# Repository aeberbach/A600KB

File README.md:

# A600KB: Mechanical keyboard Amiga A600

Like my A1200 project (see my other repos) this is a mechanical keyboard for an Amiga computer.

To make one you need:
- PCBs, which you can make by sending the contents of the 'fab' folder to your local PCB maker.
- 3D printed parts: the STL files are in the STL folder. I used a Prusa MK3S 0.25mm nozzle, Urban Grey PETG.
- 78 MX PCB-mount switches
- 32-way FFC connector (Mouser part number 538-52044-3245)
- 32-way ribbon cable (Mouser part number 538-15168-0400)
- keyswitch stabiliser for Tab and Enter keys
- one 3mm LED for CapsLock
- keycaps

For more details about design choices and putting it together please see the article on grayunicorn.com. 

Enjoy!

May 2022 Update - this is now release 2. Apart from correcting swapped keys that existed in revision 1 (see below) I made a lot of traces simpler. I used KiCAD 6 for this, it just keeps getting better. If you build a revision 2 I would love to hear about it.

Revision 1 Errata:
Many people have built it and never noticed. That goes for me too - one person contacted me and said they were having trouble with some music tracker software because it relies on the keys that are not in the right place. I had not noticed because I had not been using software that relied on those
keys - sorry if you were affected! The revision 1 PCB should be modified:

- Line 5: disconnect from MX63 (< ,) column; connect to MX79 (" ') column
- Line 7: disconnect from MX79 (" ') column; connect to MX63 (< ,) column
- Line 23: disconnect from MX79 (" ') row; connect to MX63 (< ,) row
- Line 26: disconnect from MX63 (< ,) row; connect to MX79 (" ') row

The PCB has been revised to revision 2 (the same as Commodore's schematic) now so this is fixed, but if you have a revision 1 and notice the ' and , appear to be swapped then you may need to apply this change.

Note this this project is licensed under CC BY-NC-SA 4.0 - only noncommercial use is permitted! (By all means sell the excess PCBs you get, at cost, if you order some for your own use)

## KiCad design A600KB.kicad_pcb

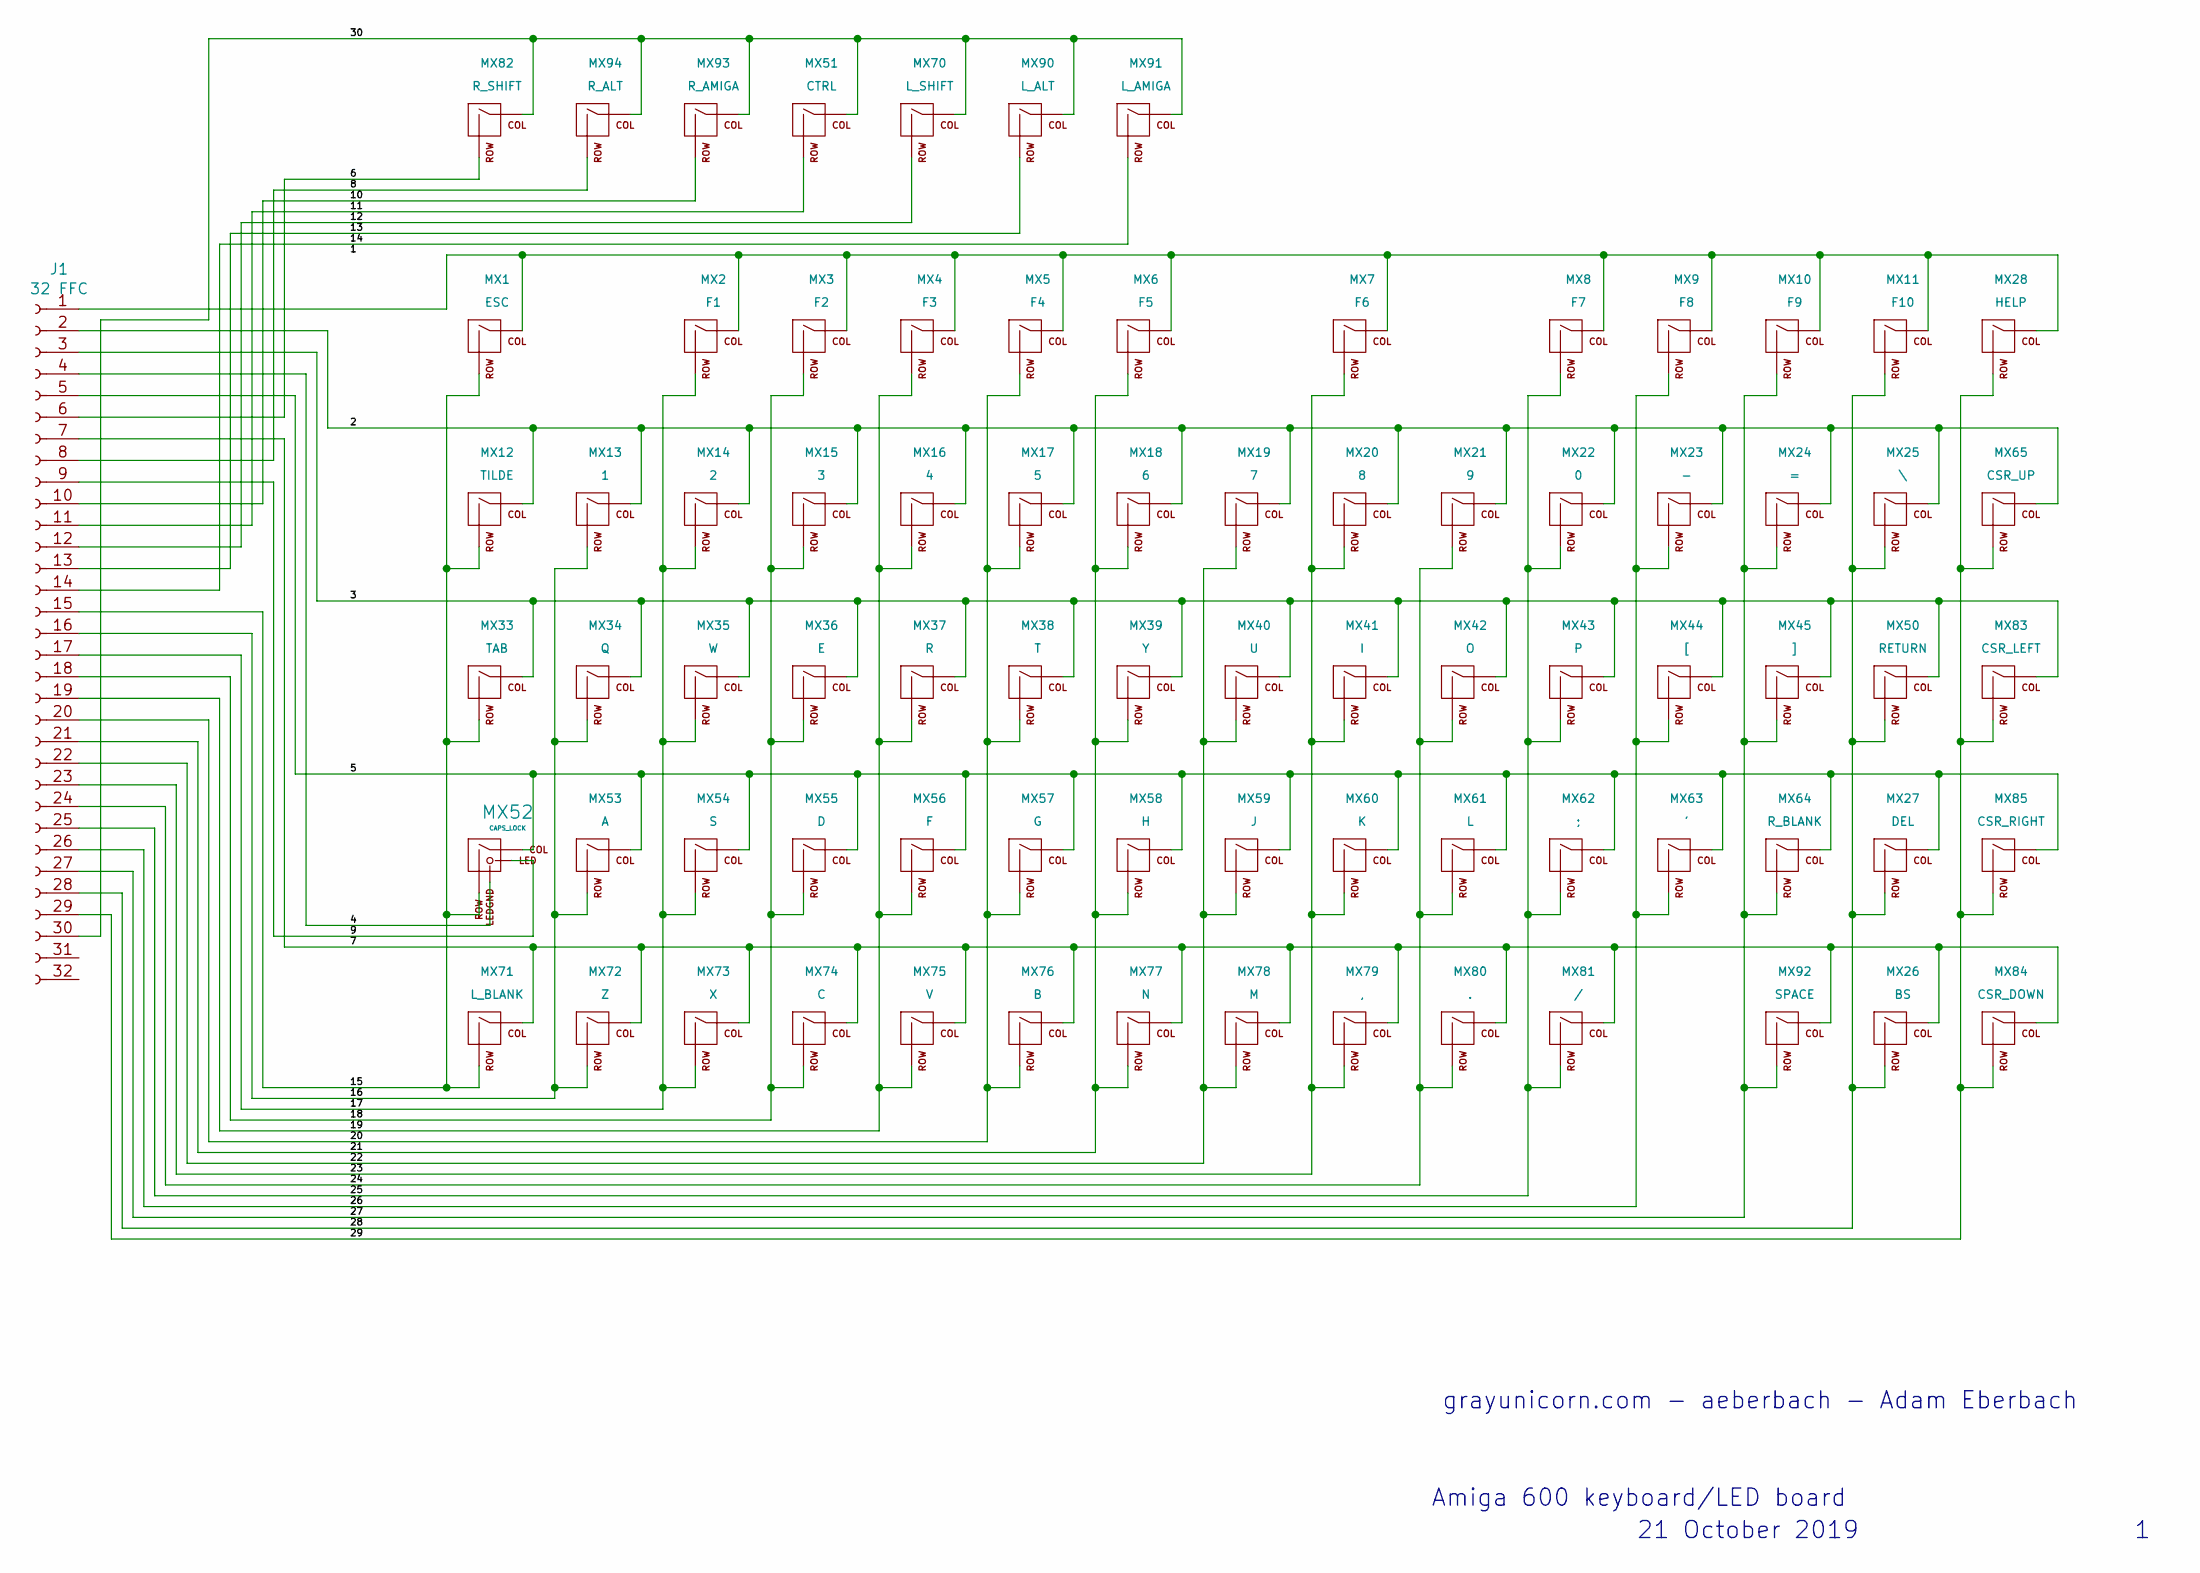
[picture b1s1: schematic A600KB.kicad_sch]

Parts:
J1: 32 FFC; FFC-1.25mm-RA-5204403245
MX1: ESC; MXOnly-1.25U-NoLED
MX2: F1; MXOnly-1.25U-NoLED
MX3: F2; MXOnly-1.25U-NoLED
MX4: F3; MXOnly-1.25U-NoLED
MX5: F4; MXOnly-1.25U-NoLED
MX6: F5; MXOnly-1.25U-NoLED
MX7: F6; MXOnly-1.25U-NoLED
MX8: F7; MXOnly-1.25U-NoLED
MX9: F8; MXOnly-1.25U-NoLED
MX10: F9; MXOnly-1.25U-NoLED
MX11: F10; MXOnly-1.25U-NoLED
MX12: TILDE; MXOnly-1.5U-NoLED
MX13: 1; MXOnly-1U-NoLED
MX14: 2; MXOnly-1U-NoLED
MX15: 3; MXOnly-1U-NoLED
MX16: 4; MXOnly-1U-NoLED
MX17: 5; MXOnly-1U-NoLED
MX18: 6; MXOnly-1U-NoLED
MX19: 7; MXOnly-1U-NoLED
MX20: 8; MXOnly-1U-NoLED
MX21: 9; MXOnly-1U-NoLED
MX22: 0; MXOnly-1U-NoLED
MX23: -; MXOnly-1U-NoLED
MX24: =; MXOnly-1U-NoLED
MX25: \; MXOnly-1U-NoLED
MX26: BS; MXOnly-1U-NoLED
MX27: DEL; MXOnly-1U-NoLED
MX28: HELP; MXOnly-1.25U-NoLED
MX33: TAB; MXOnly-2U-NoLED
MX34: Q; MXOnly-1U-NoLED
MX35: W; MXOnly-1U-NoLED
MX36: E; MXOnly-1U-NoLED
MX37: R; MXOnly-1U-NoLED
MX38: T; MXOnly-1U-NoLED
MX39: Y; MXOnly-1U-NoLED
MX40: U; MXOnly-1U-NoLED
MX41: I; MXOnly-1U-NoLED
MX42: O; MXOnly-1U-NoLED
MX43: P; MXOnly-1U-NoLED
MX44: [; MXOnly-1U-NoLED
MX45: ]; MXOnly-1U-NoLED
MX50: RETURN; MXOnly-ISO
MX51: CTRL; MXOnly-1.25U-NoLED
MX52: CAPS_LOCK; MXOnly-1U
MX53: A; MXOnly-1U-NoLED
MX54: S; MXOnly-1U-NoLED
MX55: D; MXOnly-1U-NoLED
MX56: F; MXOnly-1U-NoLED
MX57: G; MXOnly-1U-NoLED
MX58: H; MXOnly-1U-NoLED
MX59: J; MXOnly-1U-NoLED
MX60: K; MXOnly-1U-NoLED
MX61: L; MXOnly-1U-NoLED
MX62: ;; MXOnly-1U-NoLED
MX63: '; MXOnly-1U-NoLED
MX64: R_BLANK; MXOnly-1U-NoLED
MX65: CSR_UP; MXOnly-1U-NoLED
MX70: L_SHIFT; MXOnly-1.75U-NoLED
MX71: L_BLANK; MXOnly-1U-NoLED
MX72: Z; MXOnly-1U-NoLED
MX73: X; MXOnly-1U-NoLED
MX74: C; MXOnly-1U-NoLED
MX75: V; MXOnly-1U-NoLED
MX76: B; MXOnly-1U-NoLED
MX77: N; MXOnly-1U-NoLED
MX78: M; MXOnly-1U-NoLED
MX79: ,; MXOnly-1U-NoLED
MX80: .; MXOnly-1U-NoLED
MX81: /; MXOnly-1U-NoLED
MX82: R_SHIFT; MXOnly-1.75U-NoLED
MX83: CSR_LEFT; MXOnly-1U-NoLED
MX84: CSR_DOWN; MXOnly-1U-NoLED
MX85: CSR_RIGHT; MXOnly-1U-NoLED
MX90: L_ALT; MXOnly-1.25U-NoLED
MX91: L_AMIGA; MXOnly-1.25U-NoLED
MX92: SPACE; MXOnly-7U
MX93: R_AMIGA; MXOnly-1.25U-NoLED
MX94: R_ALT; MXOnly-1U-NoLED

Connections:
/2: J1.2, MX12.1 (COL), MX13.1 (COL), MX14.1 (COL), MX15.1 (COL), MX16.1 (COL), MX17.1 (COL), MX18.1 (COL), MX19.1 (COL), MX20.1 (COL), MX21.1 (COL), MX22.1 (COL), MX23.1 (COL), MX24.1 (COL), MX25.1 (COL), MX65.1 (COL)
/3: J1.3, MX33.1 (COL), MX34.1 (COL), MX35.1 (COL), MX36.1 (COL), MX37.1 (COL), MX38.1 (COL), MX39.1 (COL), MX40.1 (COL), MX41.1 (COL), MX42.1 (COL), MX43.1 (COL), MX44.1 (COL), MX45.1 (COL), MX50.1 (COL), MX83.1 (COL)
/4: J1.4, MX52.4 (LEDGND)
/5: J1.5, MX27.1 (COL), MX52.1 (COL), MX53.1 (COL), MX54.1 (COL), MX55.1 (COL), MX56.1 (COL), MX57.1 (COL), MX58.1 (COL), MX59.1 (COL), MX60.1 (COL), MX61.1 (COL), MX62.1 (COL), MX63.1 (COL), MX64.1 (COL), MX85.1 (COL)
/6: J1.6, MX82.2 (ROW)
/7: J1.7, MX26.1 (COL), MX71.1 (COL), MX72.1 (COL), MX73.1 (COL), MX74.1 (COL), MX75.1 (COL), MX76.1 (COL), MX77.1 (COL), MX78.1 (COL), MX79.1 (COL), MX80.1 (COL), MX81.1 (COL), MX84.1 (COL), MX92.1 (COL)
/8: J1.8, MX94.2 (ROW)
/9: J1.9, MX52.3 (LED)
/10: J1.10, MX93.2 (ROW)
/11: J1.11, MX51.2 (ROW)
/12: J1.12, MX70.2 (ROW)
/13: J1.13, MX90.2 (ROW)
/14: J1.14, MX91.2 (ROW)
/15: J1.15, MX1.2 (ROW), MX12.2 (ROW), MX33.2 (ROW), MX52.2 (ROW), MX71.2 (ROW)
/16: J1.16, MX13.2 (ROW), MX34.2 (ROW), MX53.2 (ROW), MX72.2 (ROW)
/17: J1.17, MX2.2 (ROW), MX14.2 (ROW), MX35.2 (ROW), MX54.2 (ROW), MX73.2 (ROW)
/18: J1.18, MX3.2 (ROW), MX15.2 (ROW), MX36.2 (ROW), MX55.2 (ROW), MX74.2 (ROW)
/19: J1.19, MX4.2 (ROW), MX16.2 (ROW), MX37.2 (ROW), MX56.2 (ROW), MX75.2 (ROW)
/20: J1.20, MX5.2 (ROW), MX17.2 (ROW), MX38.2 (ROW), MX57.2 (ROW), MX76.2 (ROW)
/21: J1.21, MX6.2 (ROW), MX18.2 (ROW), MX39.2 (ROW), MX58.2 (ROW), MX77.2 (ROW)
/22: J1.22, MX19.2 (ROW), MX40.2 (ROW), MX59.2 (ROW), MX78.2 (ROW)
/23: J1.23, MX7.2 (ROW), MX20.2 (ROW), MX41.2 (ROW), MX60.2 (ROW), MX79.2 (ROW)
/24: J1.24, MX21.2 (ROW), MX42.2 (ROW), MX61.2 (ROW), MX80.2 (ROW)
/25: J1.25, MX8.2 (ROW), MX22.2 (ROW), MX43.2 (ROW), MX62.2 (ROW), MX81.2 (ROW)
/26: J1.26, MX9.2 (ROW), MX23.2 (ROW), MX44.2 (ROW), MX63.2 (ROW)
/27: J1.27, MX10.2 (ROW), MX24.2 (ROW), MX45.2 (ROW), MX64.2 (ROW), MX92.2 (ROW)
/28: J1.28, MX11.2 (ROW), MX25.2 (ROW), MX26.2 (ROW), MX27.2 (ROW), MX50.2 (ROW)
/29: J1.29, MX28.2 (ROW), MX65.2 (ROW), MX83.2 (ROW), MX84.2 (ROW), MX85.2 (ROW)
/30: J1.30, MX51.1 (COL), MX70.1 (COL), MX82.1 (COL), MX90.1 (COL), MX91.1 (COL), MX93.1 (COL), MX94.1 (COL)
unnamed: J1.1, MX1.1 (COL), MX2.1 (COL), MX3.1 (COL), MX4.1 (COL), MX5.1 (COL), MX6.1 (COL), MX7.1 (COL), MX8.1 (COL), MX9.1 (COL), MX10.1 (COL), MX11.1 (COL), MX28.1 (COL)

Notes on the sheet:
21 October 2019
grayunicorn.com - aeberbach - Adam Eberbach
Amiga 600 keyboard/LED board

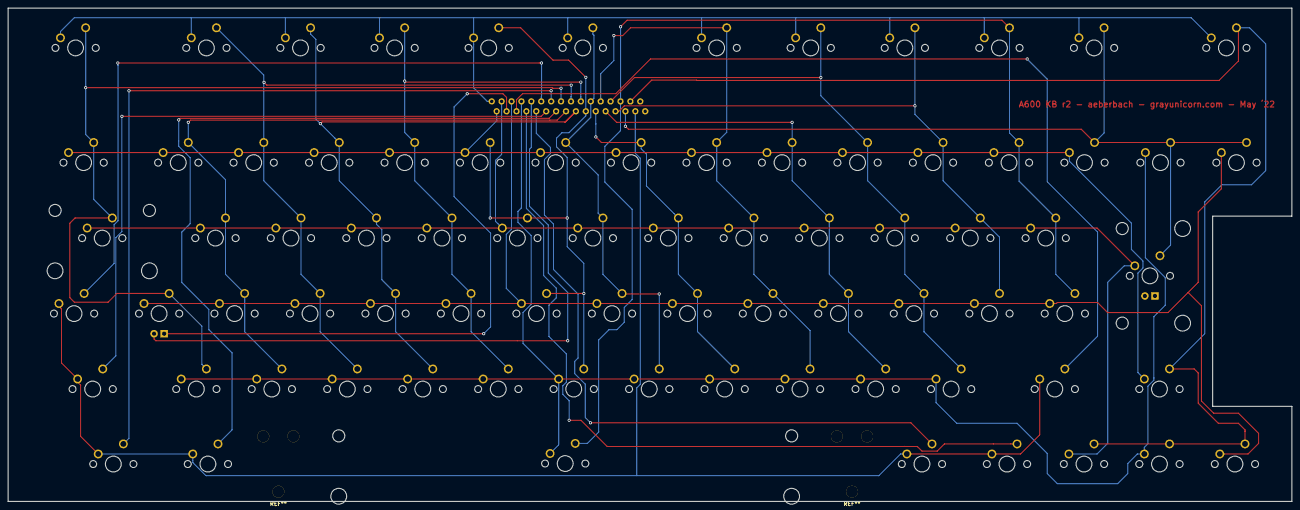
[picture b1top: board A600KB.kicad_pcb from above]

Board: 2 copper layers, 324.0 x 124.5 mm, 79 parts (1 on the bottom side), 30 nets.

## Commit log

2019-10-21 Schematic without connectors
2019-10-21 footprints for connectors
2019-10-21 correct annotations
2019-11-19 Finished, sent to fab
    PCB Order
    Weight:
    1kg
    Project Name:
    A600 r1
    Length:
2019-12-17 STIL files for 3D-printed parts
2019-12-17 Add license
2020-01-02 A link that will open an A600 keyboard layout
    keyboard-layout-editor.com
2022-01-16 How to fix
2022-01-16 typo
2022-04-13 README fix instructions; new Kicad version update
2022-04-13 update kicad version
2022-04-13 formatting
2022-05-16 Revise PCB to fix swapped keys
2023-03-10 info about getting keycaps
2024-05-24 Add note about keyboard fix
2024-06-19 CC-BY-NC-SA
2024-06-19 Use A600
2024-06-30 OPened with KiCAD 8
